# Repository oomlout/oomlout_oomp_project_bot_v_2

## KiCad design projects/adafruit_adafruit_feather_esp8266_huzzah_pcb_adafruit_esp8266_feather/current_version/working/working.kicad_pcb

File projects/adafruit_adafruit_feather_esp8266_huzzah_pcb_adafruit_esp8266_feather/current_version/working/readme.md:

# adafruit_feather_esp8266_huzzah_pcb
 
## summary 
* id: adafruit_adafruit_feather_esp8266_huzzah_pcb_adafruit_esp8266_feather
* user: adafruit
* name: adafruit_feather_esp8266_huzzah_pcb
* board: adafruit_esp8266_feather
* repo: https://github.com/adafruit/Adafruit-Feather-ESP8266-HUZZAH-PCB

* src_file_repo_sch: 
* src_file_repo_sch_link: https://github.com/adafruit/Adafruit-Feather-ESP8266-HUZZAH-PCB/tree/master/
* full details link: https://github.com/oomlout/oomlout_oomp_project_bot_v_2/tree/main/projects/adafruit_adafruit_feather_esp8266_huzzah_pcb_adafruit_esp8266_feather/current_version/working  

## schematic  
  
[schematic (pdf)](working_schematic.pdf) 

## pcb  

[board (pdf)](working.pdf)  

## working_bom
| Id | Designator | Footprint | Quantity | Designation | Supplier and ref |  | None | 
| --- | --- | --- | --- | --- | --- | --- | --- | 
| 1 | R2,R10 | 0603-NO | 2 | 1K |  |  | [''] | 
| 2 | CHG0 | CHIPLED_0805_NOOUTLINE | 1 | ORANGE |  |  | [''] | 
| 3 | JP1 | 1X16_ROUND | 1 |  |  |  | [''] | 
| 4 | R3,R5,R9,R4,R1,R7 | 0603-NO | 6 | 10K |  |  | [''] | 
| 5 | X4 | 4UCONN_20329_V2 | 1 | 20329 |  |  | [''] | 
| 6 | U$34,U$35 | FIDUCIAL_1MM | 2 | FIDUCIAL_1MM |  |  | [''] | 
| 7 | IC1 | QFN24_4MM_SMSC | 1 | CP2104 |  |  | [''] | 
| 8 | U$31,U$32 | MOUNTINGHOLE_2.5_PLATED | 2 | MOUNTINGHOLE2.5 |  |  | [''] | 
| 9 | @HOLE0,@HOLE1 |  | 2 |  |  |  | [''] | 
| 10 | X2 | ESP-12S | 1 | ESP-12 |  |  | [''] | 
| 11 | Q2,Q1 | SOT23-3 | 2 | mmbt2222 |  |  | [''] | 
| 12 | C3,C6,C8 | 0805-NO | 3 | 10ÂµF |  |  | [''] | 
| 13 | R11 | _0603MP | 1 | 1K |  |  | [''] | 
| 14 | D3 | CHIPLED_0805_NOOUTLINE | 1 | RED |  |  | [''] | 
| 15 | R6 | 0603-NO | 1 | 4.7K |  |  | [''] | 
| 16 | U2 | SOT23-5 | 1 | AP2112-3.3 |  |  | [''] | 
| 17 | X1 | JSTPH2 | 1 | JSTPH |  |  | [''] | 
| 18 | SW2 | BTN_KMR2_4.6X2.8 | 1 | KMR2 |  |  | [''] | 
| 19 | D4 | SOD-123 | 1 | MBR120 |  |  | [''] | 
| 20 | SJ1 | SOLDERJUMPER_CLOSEDWIRE | 1 |  |  |  | [''] | 
| 21 | JP3 | 1X12_ROUND | 1 |  |  |  | [''] | 
| 22 | U$15 | ADAFRUIT_3.5MM | 1 |  |  |  | [''] | 
| 23 | R8 | 0603-NO | 1 | 10K\ |  |  | [''] | 
| 24 | C7 | 0603-NO | 1 | 1uF |  |  | [''] | 
| 25 | U3 | SOT23-5 | 1 | MCP73831T-2ACI/OT |  |  | [''] | 
| 26 | C2 | 0805-NO | 1 | 10uF |  |  | [''] | 
| 27 | U$23 | HUZZAHLOGO | 1 |  |  |  | [''] | 
| 28 | U$13 | PCBFEAT-REV-040 | 1 |  |  |  | [''] | 
| 29 | U$7 | ADAFRUIT_5MM | 1 |  |  |  | [''] | 
| 30 | U$9 | FEATHERLOGO | 1 |  |  |  | [''] | 

## bom_schematic
| Ref | Qnty | Value | Cmp name | Footprint | Description | Vendor | DNP | 
| --- | --- | --- | --- | --- | --- | --- | --- | 
| C2 | 1 | 10uF | CAP_CERAMIC0805-NOOUTLINE | working:0805-NO |  |  |  | 
| C3, C6, C8 | 3 | 10ÂµF | CAP_CERAMIC0805-NOOUTLINE | working:0805-NO |  |  |  | 
| C7 | 1 | 1uF | CAP_CERAMIC0603_NO | working:0603-NO |  |  |  | 
| CHG0 | 1 | ORANGE | LED0805_NOOUTLINE | working:CHIPLED_0805_NOOUTLINE |  |  |  | 
| D3 | 1 | RED | LED0805_NOOUTLINE | working:CHIPLED_0805_NOOUTLINE |  |  |  | 
| D4 | 1 | MBR120 | DIODE-SCHOTTKYSOD-123 | working:SOD-123 |  |  |  | 
| IC1 | 1 | CP2104 | CP2104 | working:QFN24_4MM_SMSC |  |  |  | 
| JP1 | 1 | HEADER-1X16ROUND | HEADER-1X16ROUND | working:1X16_ROUND |  |  |  | 
| JP3 | 1 | HEADER-1X12 | HEADER-1X12 | working:1X12_ROUND |  |  |  | 
| Q1, Q2 | 2 | mmbt2222 | TRANSISTOR_NPNSOT23-3 | working:SOT23-3 |  |  |  | 
| R1, R3, R4, R5, R7, R9 | 6 | 10K | RESISTOR_0603_NOOUT | working:0603-NO |  |  |  | 
| R2, R10 | 2 | 1K | RESISTOR_0603_NOOUT | working:0603-NO |  |  |  | 
| R6 | 1 | 4.7K | RESISTOR_0603_NOOUT | working:0603-NO |  |  |  | 
| R8 | 1 | 10K\ | RESISTOR_0603_NOOUT | working:0603-NO |  |  |  | 
| R11 | 1 | 1K | RESISTOR_0603MP | working:_0603MP |  |  |  | 
| SJ1 | 1 | SOLDERJUMPER_CLOSED | SOLDERJUMPER_CLOSED | working:SOLDERJUMPER_CLOSEDWIRE |  |  |  | 
| SW2 | 1 | KMR2 | SWITCH_TACT_SMT4.6X2.8 | working:BTN_KMR2_4.6X2.8 |  |  |  | 
| U2 | 1 | AP2112-3.3 | VREG_SOT23-5 | working:SOT23-5 |  |  |  | 
| U3 | 1 | MCP73831T-2ACI/OT | MCP73831/2 | working:SOT23-5 |  |  |  | 
| U$31, U$32 | 2 | MOUNTINGHOLE2.5 | MOUNTINGHOLE2.5 | working:MOUNTINGHOLE_2.5_PLATED |  |  |  | 
| U$34, U$35 | 2 | FIDUCIAL_1MM | FIDUCIAL_1MM | working:FIDUCIAL_1MM |  |  |  | 
| X1 | 1 | JSTPH | CON_JST_PH_2PIN | working:JSTPH2 |  |  |  | 
| X2 | 1 | ESP-12S | ESP-12S | working:ESP-12S |  |  |  | 
| X4 | 1 | 20329 | USB_MICRO_20329_V2 | working:4UCONN_20329_V2 |  |  |  | 

## mounting_holes
| x | y | package | value | ref | size | 
| --- | --- | --- | --- | --- | --- | 
| 0.0 | 17.78 | MOUNTINGHOLE_2.5_PLATED | MOUNTINGHOLE2.5 | U$31 | m3 | 
| 0.0 | 0.0 | MOUNTINGHOLE_2.5_PLATED | MOUNTINGHOLE2.5 | U$32 | m3 |

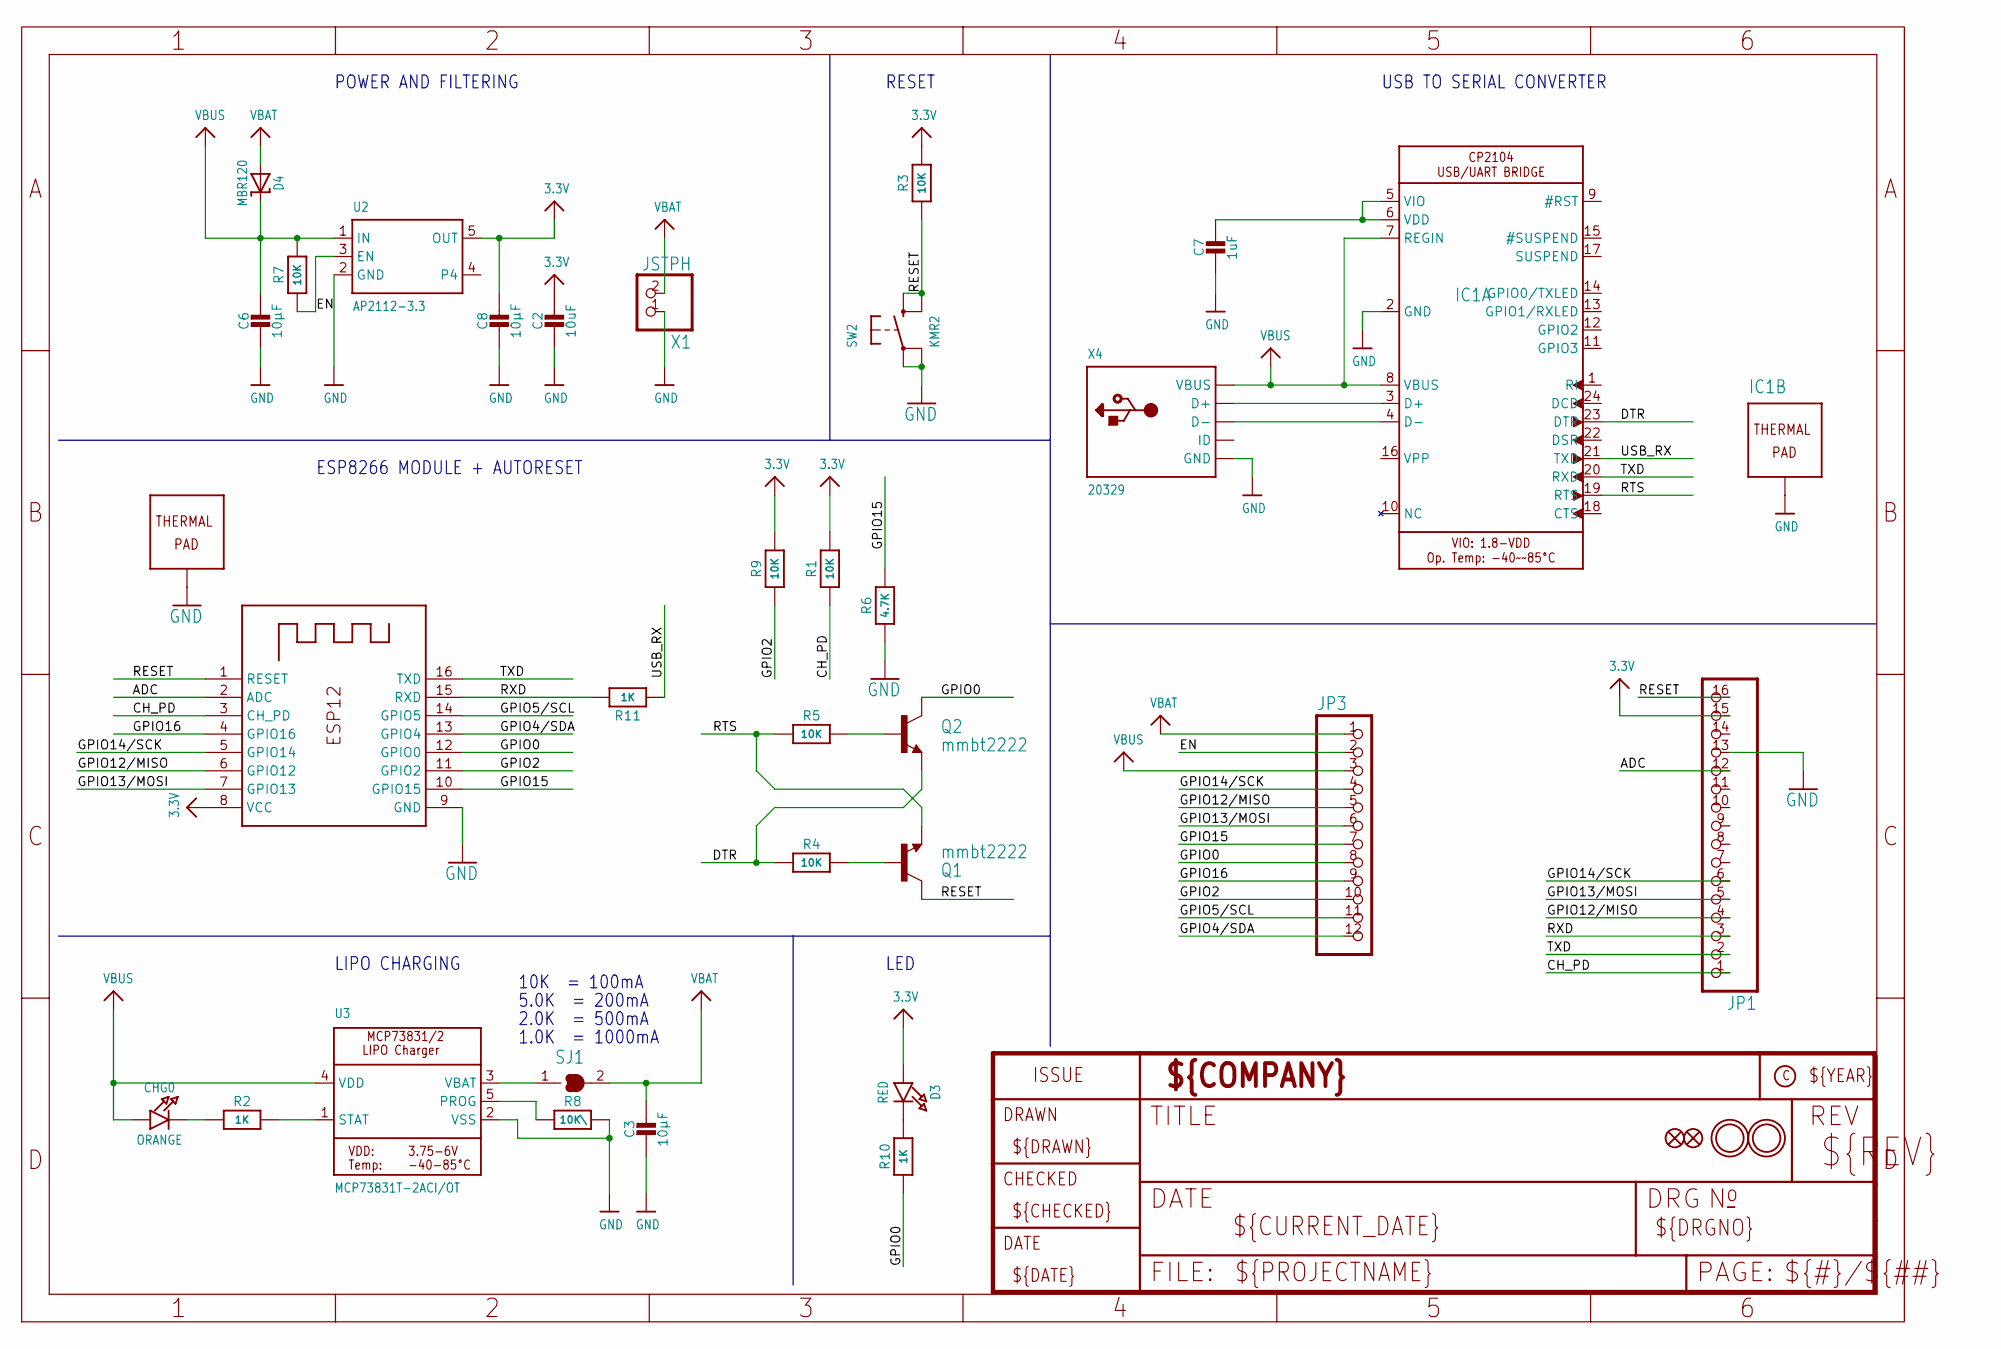
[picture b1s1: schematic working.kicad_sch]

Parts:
C2: 10uF; 0805-NO
C3, C6, C8: 10µF; 0805-NO
C7: 1uF; 0603-NO
CHG0: ORANGE; CHIPLED_0805_NOOUTLINE
D3: RED; CHIPLED_0805_NOOUTLINE
D4: MBR120; SOD-123
IC1: CP2104; QFN24_4MM_SMSC
JP1: HEADER-1X16ROUND; 1X16_ROUND
JP3: HEADER-1X12; 1X12_ROUND
Q1, Q2: mmbt2222; SOT23-3
R1, R3, R4, R5, R7, R9: 10K; 0603-NO
R2, R10: 1K; 0603-NO
R6: 4.7K; 0603-NO
R8: 10K\; 0603-NO
R11: 1K; _0603MP
SJ1: SOLDERJUMPER_CLOSED; SOLDERJUMPER_CLOSEDWIRE
SW2: KMR2; BTN_KMR2_4.6X2.8
U2: AP2112-3.3; SOT23-5
U3: MCP73831T-2ACI/OT; SOT23-5
U$31, U$32: MOUNTINGHOLE2.5; MOUNTINGHOLE_2.5_PLATED
U$34, U$35: FIDUCIAL_1MM
X1: JSTPH; JSTPH2
X2: ESP-12S
X4: 20329; 4UCONN_20329_V2

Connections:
3.3V: C2.1, C8.1, D3.A, JP1.15, R1.2, R3.2, R9.2, U2.5 (OUT), X2.8 (VCC)
ADC: JP1.12, X2.2 (ADC)
CH_PD: JP1.1, R1.1, X2.3 (CH_PD)
DTR: IC1.23 (DTR), Q2.2 (E), R4.1
EN: JP3.2, R7.1, U2.3 (EN)
GND: C2.2, C3.2, C6.2, C7.2, C8.2, IC1.2 (GND), IC1.THERM (TP), JP1.13, R6.1, R8.2, SW2.A, SW2.A' (P1), U2.2 (GND), U3.2 (VSS), X1.1, X2.9 (GND), X2.P$1 (TP), X4.BASE@1 (GND), X4.BASE@2 (GND), X4.GND, X4.SPRT@1 (GND), X4.SPRT@2 (GND), X4.SPRT@3 (GND), X4.SPRT@4 (GND)
GPIO0: JP3.8, Q2.3 (C), R10.1, X2.12 (GPIO0)
GPIO2: JP3.10, R9.1, X2.11 (GPIO2)
GPIO4/SDA: JP3.12, X2.13 (GPIO4)
GPIO5/SCL: JP3.11, X2.14 (GPIO5)
GPIO12/MISO: JP1.4, JP3.5, X2.6 (GPIO12)
GPIO13/MOSI: JP1.5, JP3.6, X2.7 (GPIO13)
GPIO14/SCK: JP1.6, JP3.4, X2.5 (GPIO14)
GPIO15: JP3.7, R6.2, X2.10 (GPIO15)
GPIO16: JP3.9, X2.4 (GPIO16)
unnamed: CHG0.C, R2.1
unnamed: IC1.3 (D+), X4.D+
unnamed: R2.2, U3.1 (STAT)
unnamed: R8.1, U3.5 (PROG)
unnamed: D3.C, R10.2
unnamed: IC1.4 (D-), X4.D-
unnamed: SJ1.1, U3.3 (VBAT)
unnamed: C7.1, IC1.5 (VIO), IC1.6 (VDD)
unnamed: Q1.1 (B), R4.2
unnamed: Q2.1 (B), R5.2
RESET: JP1.16, Q1.3 (C), R3.1, SW2.B (S), SW2.B' (S1), X2.1 (RESET)
RTS: IC1.19 (RTS), Q1.2 (E), R5.1
RXD: JP1.3, R11.2, X2.15 (RXD)
TXD: IC1.20 (RXD), JP1.2, X2.16 (TXD)
USB_RX: IC1.21 (TXD), R11.1
VBAT: C3.1, D4.A, JP3.1, SJ1.2, X1.2
VBUS: C6.1, CHG0.A, D4.C, IC1.7 (REGIN), IC1.8 (VBUS), JP3.3, R7.2, U2.1 (IN), U3.4 (VDD), X4.VBUS

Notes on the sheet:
10K = 100mA
POWER AND FILTERING
1.0K = 1000mA
5.0K = 200mA
USB TO SERIAL CONVERTER
2.0K = 500mA
LED
ESP8266 MODULE + AUTORESET
RESET
LIPO CHARGING

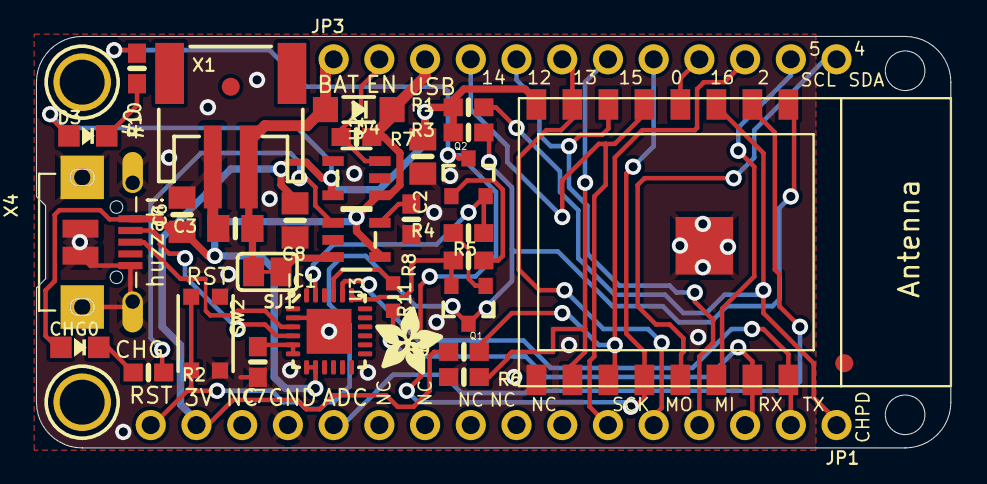
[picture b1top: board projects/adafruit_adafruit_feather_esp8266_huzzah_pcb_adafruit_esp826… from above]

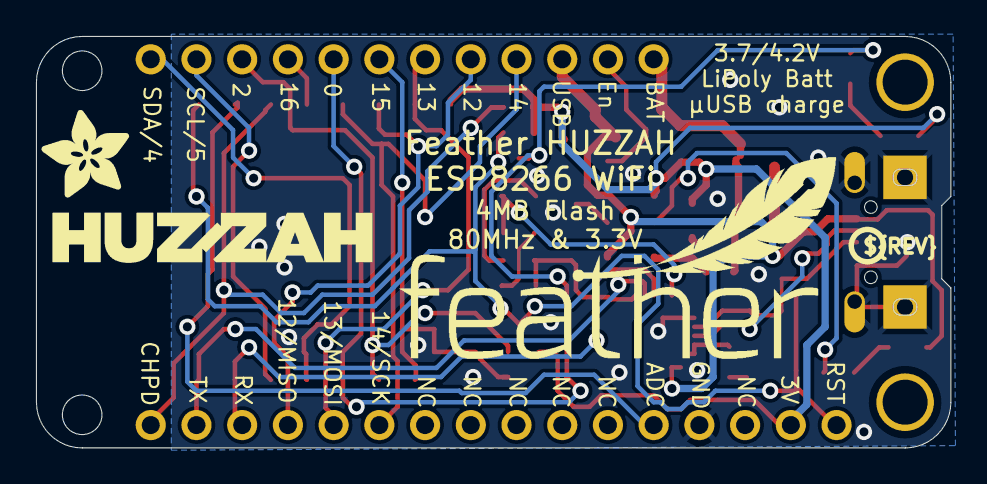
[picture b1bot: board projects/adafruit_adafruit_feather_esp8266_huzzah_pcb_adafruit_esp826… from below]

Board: 2 copper layers, 50.8 x 22.9 mm, 42 parts (4 on the bottom side), 32 nets.

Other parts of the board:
@HOLE0, @HOLE1: (no value)
U$7: ADAFRUIT_5MM
U$9: FEATHERLOGO
U$13: PCBFEAT-REV-040
U$15: ADAFRUIT_3.5MM
U$23: HUZZAHLOGO

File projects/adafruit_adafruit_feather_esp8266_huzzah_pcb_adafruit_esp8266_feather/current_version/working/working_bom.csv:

"Id";"Designator";"Footprint";"Quantity";"Designation";"Supplier and ref";
1;"R2,R10";"0603-NO";2;"1K";;;
2;"CHG0";"CHIPLED_0805_NOOUTLINE";1;"ORANGE";;;
3;"JP1";"1X16_ROUND";1;"";;;
4;"R3,R5,R9,R4,R1,R7";"0603-NO";6;"10K";;;
5;"X4";"4UCONN_20329_V2";1;"20329";;;
6;"U$34,U$35";"FIDUCIAL_1MM";2;"FIDUCIAL_1MM";;;
7;"IC1";"QFN24_4MM_SMSC";1;"CP2104";;;
8;"U$31,U$32";"MOUNTINGHOLE_2.5_PLATED";2;"MOUNTINGHOLE2.5";;;
9;"@HOLE0,@HOLE1";"";2;"";;;
10;"X2";"ESP-12S";1;"ESP-12";;;
11;"Q2,Q1";"SOT23-3";2;"mmbt2222";;;
12;"C3,C6,C8";"0805-NO";3;"10µF";;;
13;"R11";"_0603MP";1;"1K";;;
14;"D3";"CHIPLED_0805_NOOUTLINE";1;"RED";;;
15;"R6";"0603-NO";1;"4.7K";;;
16;"U2";"SOT23-5";1;"AP2112-3.3";;;
17;"X1";"JSTPH2";1;"JSTPH";;;
18;"SW2";"BTN_KMR2_4.6X2.8";1;"KMR2";;;
19;"D4";"SOD-123";1;"MBR120";;;
20;"SJ1";"SOLDERJUMPER_CLOSEDWIRE";1;"";;;
21;"JP3";"1X12_ROUND";1;"";;;
22;"U$15";"ADAFRUIT_3.5MM";1;"";;;
23;"R8";"0603-NO";1;"10K\";;;
24;"C7";"0603-NO";1;"1uF";;;
25;"U3";"SOT23-5";1;"MCP73831T-2ACI/OT";;;
26;"C2";"0805-NO";1;"10uF";;;
27;"U$23";"HUZZAHLOGO";1;"";;;
28;"U$13";"PCBFEAT-REV-040";1;"";;;
29;"U$7";"ADAFRUIT_5MM";1;"";;;
30;"U$9";"FEATHERLOGO";1;"";;;

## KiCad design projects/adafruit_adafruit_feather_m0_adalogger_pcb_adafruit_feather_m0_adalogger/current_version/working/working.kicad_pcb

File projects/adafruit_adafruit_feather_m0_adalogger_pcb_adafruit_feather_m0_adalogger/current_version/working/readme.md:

# adafruit_feather_m0_adalogger_pcb
 
## summary 
* id: adafruit_adafruit_feather_m0_adalogger_pcb_adafruit_feather_m0_adalogger
* user: adafruit
* name: adafruit_feather_m0_adalogger_pcb
* board: adafruit_feather_m0_adalogger
* repo: https://github.com/adafruit/Adafruit-Feather-M0-Adalogger-PCB

* src_file_repo_sch: 
* src_file_repo_sch_link: https://github.com/adafruit/Adafruit-Feather-M0-Adalogger-PCB/tree/master/
* full details link: https://github.com/oomlout/oomlout_oomp_project_bot_v_2/tree/main/projects/adafruit_adafruit_feather_m0_adalogger_pcb_adafruit_feather_m0_adalogger/current_version/working  

## schematic  
  
[schematic (pdf)](working_schematic.pdf) 

## pcb  

[board (pdf)](working.pdf)  

## working_bom
| Id | Designator | Footprint | Quantity | Designation | Supplier and ref |  | None | 
| --- | --- | --- | --- | --- | --- | --- | --- | 
| 1 | C5 | 0805-NO | 1 | 10uF |  |  | [''] | 
| 2 | CHG0 | CHIPLED_0805_NOOUTLINE | 1 | ORANGE |  |  | [''] | 
| 3 | C6,C8,C3 | 0805-NO | 3 | 10ÂµF |  |  | [''] | 
| 4 | X4 | MICROSD | 1 | microsd |  |  | [''] | 
| 5 | SW1 | KMR2 | 1 | SPST_TACT-KMR2 |  |  | [''] | 
| 6 | R6 | 0603-NO | 1 | 100K |  |  | [''] | 
| 7 | C7,C1,C14 | 0603-NO | 3 | 1uF |  |  | [''] | 
| 8 | C4,C2 | 0603-NO | 2 | 22pF |  |  | [''] | 
| 9 | R3,R1 | 0603-NO | 2 | 100k |  |  | [''] | 
| 10 | X2 | XTAL3215 | 1 | 32.768 |  |  | [''] | 
| 11 | @HOLE1,@HOLE0 |  | 2 |  |  |  | [''] | 
| 12 | U$34,U$35 | FIDUCIAL_1MM | 2 | FIDUCIAL" |  |  | [''] | 
| 13 | U$7 | ADAFRUIT_3.5MM | 1 |  |  |  | [''] | 
| 14 | U2 | SOT23-5 | 1 | SPX3819-3.3 |  |  | [''] | 
| 15 | U$31,U$32 | MOUNTINGHOLE_2.5_PLATED | 2 | MOUNTINGHOLE2.5 |  |  | [''] | 
| 16 | JP1 | 1X16_ROUND | 1 |  |  |  | [''] | 
| 17 | L0 | CHIPLED_0805_NOOUTLINE | 1 | RED |  |  | [''] | 
| 18 | L1 | CHIPLED_0805_NOOUTLINE | 1 | GREEN |  |  | [''] | 
| 19 | X3 | 4UCONN_20329_V2 | 1 | microUSB |  |  | [''] | 
| 20 | R4,R2 | 0603-NO | 2 | 1K |  |  | [''] | 
| 21 | JP3 | 1X12_ROUND | 1 |  |  |  | [''] | 
| 22 | U$9 | PCBFEAT-REV-040 | 1 |  |  |  | [''] | 
| 23 | D1 | SOD-123 | 1 | MBR120 |  |  | [''] | 
| 24 | R7 | 0603-NO | 1 | 2.2K |  |  | [''] | 
| 25 | U3 | SOT23-5 | 1 | MCP73831T-2ACI/OT |  |  | [''] | 
| 26 | X1 | JSTPH2 | 1 | JSTPH |  |  | [''] | 
| 27 | R8 | 0603-NO | 1 | 10K\ |  |  | [''] | 
| 28 | U$4 | TQFN48_7MM | 1 | ATSAMD21G18_QFN |  |  | [''] | 
| 29 | U$14 | ADALOGGER_LOGO | 1 |  |  |  | [''] | 
| 30 | TP1,TP2 | TESTPOINT_ROUND_1.5MM | 2 |  |  |  | [''] | 
| 31 | U$13 | FEATHERLOGO | 1 |  |  |  | [''] | 

## bom_schematic
| Ref | Qnty | Value | Cmp name | Footprint | Description | Vendor | DNP | 
| --- | --- | --- | --- | --- | --- | --- | --- | 
| C1, C7, C14 | 3 | 1uF | CAP_CERAMIC0603_NO | working:0603-NO |  |  |  | 
| C2, C4 | 2 | 22pF | CAP_CERAMIC0603_NO | working:0603-NO |  |  |  | 
| C3, C6, C8 | 3 | 10ÂµF | CAP_CERAMIC0805-NOOUTLINE | working:0805-NO |  |  |  | 
| C5 | 1 | 10uF | CAP_CERAMIC0805-NOOUTLINE | working:0805-NO |  |  |  | 
| CHG0 | 1 | ORANGE | LED0805_NOOUTLINE | working:CHIPLED_0805_NOOUTLINE |  |  |  | 
| D1 | 1 | MBR120 | DIODE-SCHOTTKYSOD-123 | working:SOD-123 |  |  |  | 
| JP1 | 1 | HEADER-1X16ROUND | HEADER-1X16ROUND | working:1X16_ROUND |  |  |  | 
| JP3 | 1 | HEADER-1X12 | HEADER-1X12 | working:1X12_ROUND |  |  |  | 
| L0 | 1 | RED | LED0805_NOOUTLINE | working:CHIPLED_0805_NOOUTLINE |  |  |  | 
| L1 | 1 | GREEN | LED0805_NOOUTLINE | working:CHIPLED_0805_NOOUTLINE |  |  |  | 
| R1, R3 | 2 | 100k | RESISTOR_0603_NOOUT | working:0603-NO |  |  |  | 
| R2, R4 | 2 | 1K | RESISTOR_0603_NOOUT | working:0603-NO |  |  |  | 
| R6 | 1 | 100K | RESISTOR_0603_NOOUT | working:0603-NO |  |  |  | 
| R7 | 1 | 2.2K | RESISTOR_0603_NOOUT | working:0603-NO |  |  |  | 
| R8 | 1 | 10K\ | RESISTOR_0603_NOOUT | working:0603-NO |  |  |  | 
| SW1 | 1 | SPST_TACT-KMR2 | SPST_TACT-KMR2 | working:KMR2 |  |  |  | 
| TP1, TP2 | 2 | TESTPOINTROUND1.5MM | TESTPOINTROUND1.5MM | working:TESTPOINT_ROUND_1.5MM |  |  |  | 
| U2 | 1 | SPX3819-3.3 | VREG_SOT23-5 | working:SOT23-5 |  |  |  | 
| U3 | 1 | MCP73831T-2ACI/OT | MCP73831/2 | working:SOT23-5 |  |  |  | 
| U$4 | 1 | ATSAMD21J_QFN | ATSAMD21J_QFN | working:TQFN48_7MM |  |  |  | 
| U$31, U$32 | 2 | MOUNTINGHOLE2.5 | MOUNTINGHOLE2.5 | working:MOUNTINGHOLE_2.5_PLATED |  |  |  | 
| U$34, U$35 | 2 | FIDUCIAL"" | FIDUCIAL{dblquote}{dblquote} | working:FIDUCIAL_1MM |  |  |  | 
| X1 | 1 | JSTPH | CON_JST_PH_2PIN | working:JSTPH2 |  |  |  | 
| X2 | 1 | 32.768 | XTAL-3.2X1.5 | working:XTAL3215 |  |  |  | 
| X3 | 1 | microUSB | USB_MICRO_20329_V2 | working:4UCONN_20329_V2 |  |  |  | 
| X4 | 1 | microsd | MICROSD | working:MICROSD |  |  |  | 

## mounting_holes
| x | y | package | value | ref | size | 
| --- | --- | --- | --- | --- | --- | 
| 0.0 | 17.78 | MOUNTINGHOLE_2.5_PLATED | MOUNTINGHOLE2.5 | U$31 | m3 | 
| 0.0 | 0.0 | MOUNTINGHOLE_2.5_PLATED | MOUNTINGHOLE2.5 | U$32 | m3 |

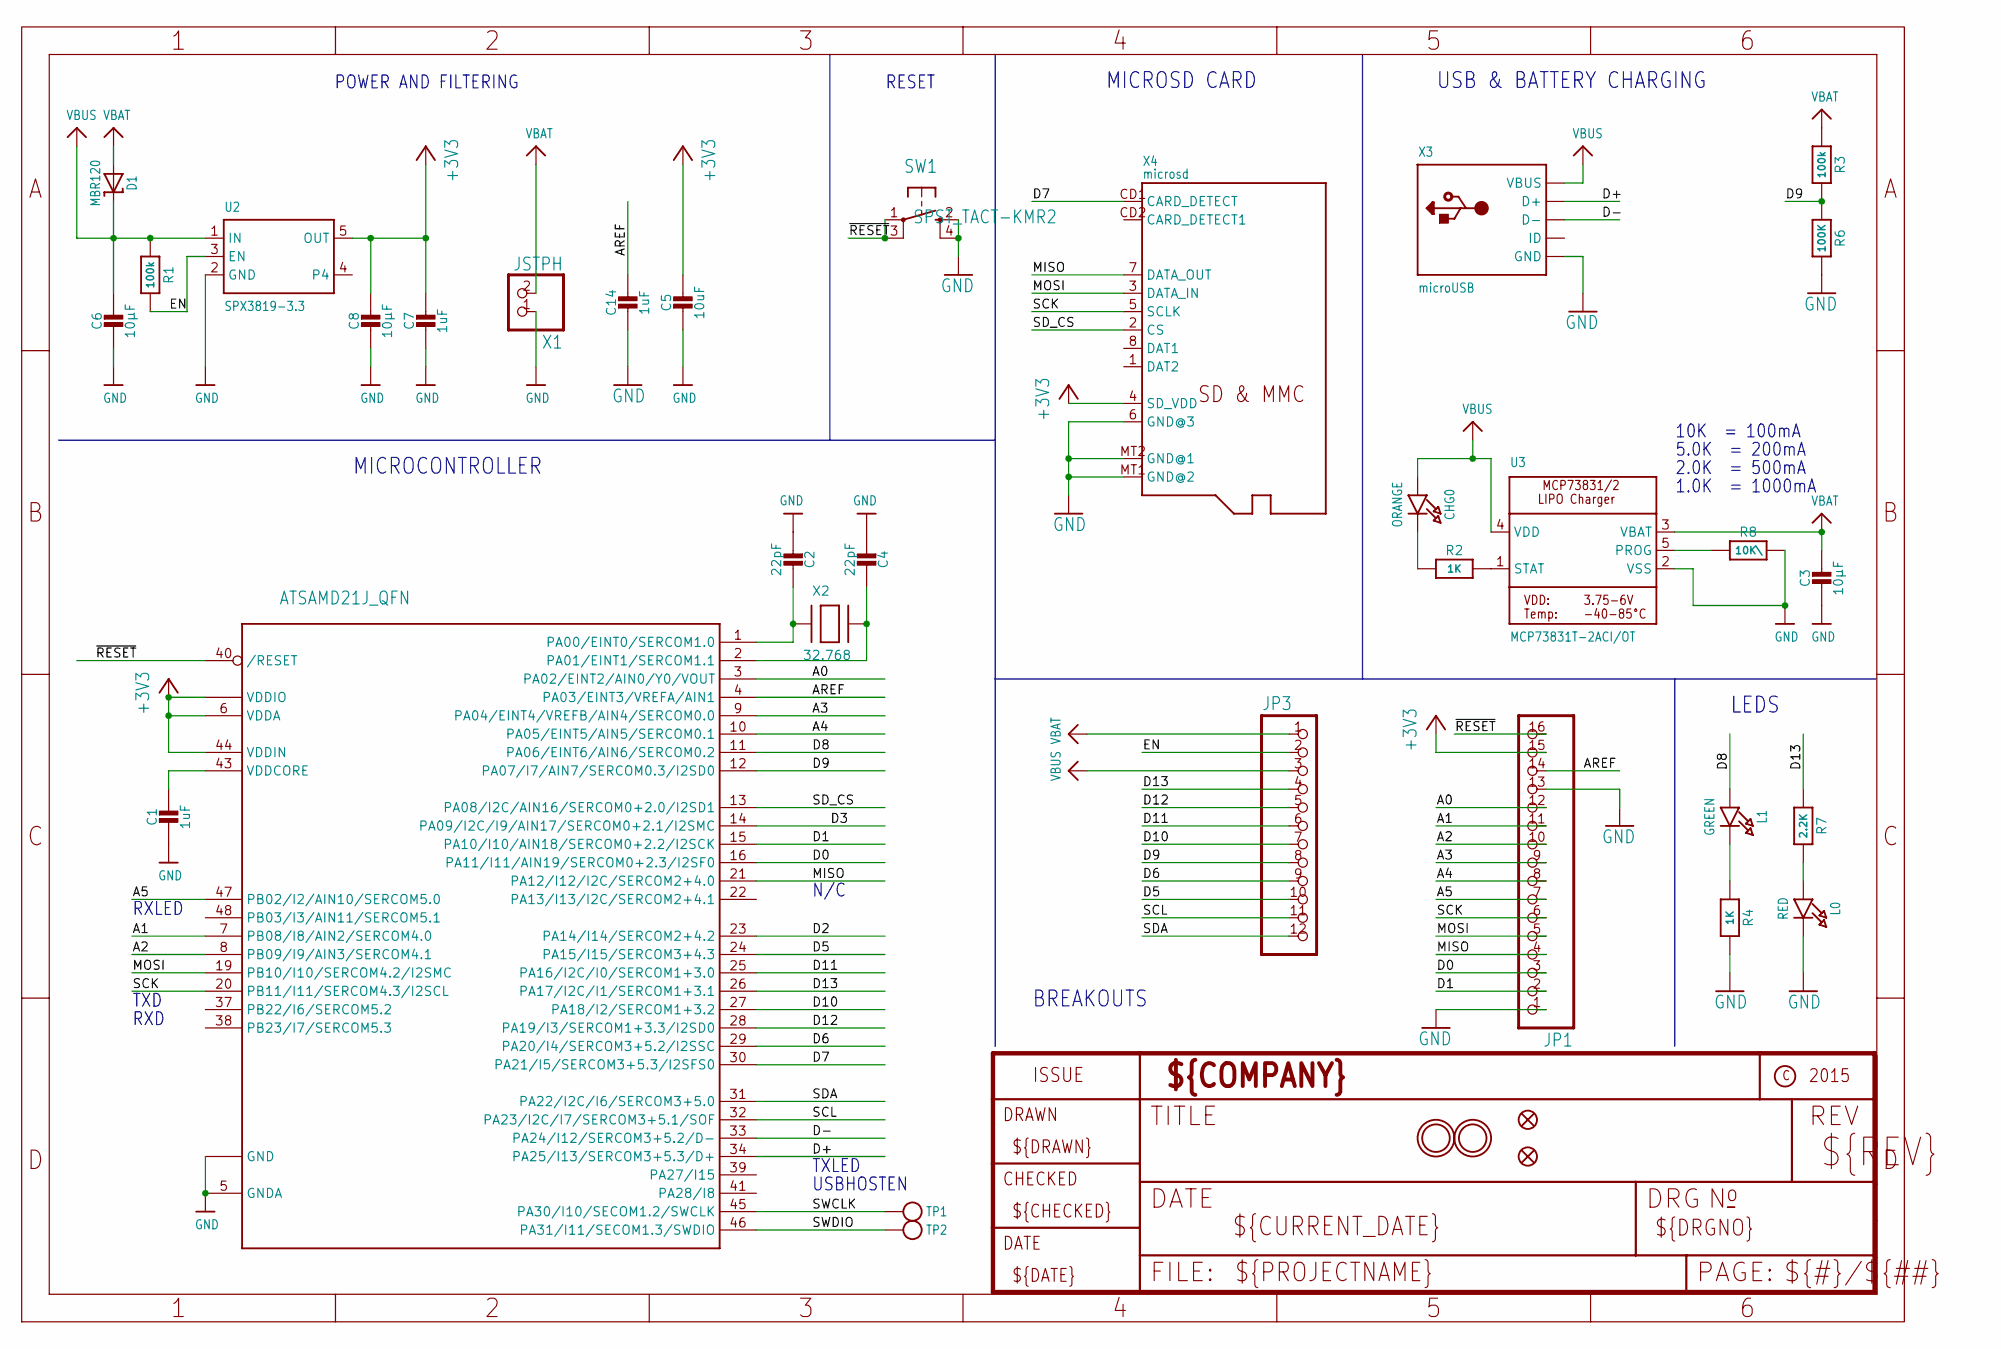
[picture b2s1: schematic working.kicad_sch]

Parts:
C1, C7, C14: 1uF; 0603-NO
C2, C4: 22pF; 0603-NO
C3, C6, C8: 10µF; 0805-NO
C5: 10uF; 0805-NO
CHG0: ORANGE; CHIPLED_0805_NOOUTLINE
D1: MBR120; SOD-123
JP1: HEADER-1X16ROUND; 1X16_ROUND
JP3: HEADER-1X12; 1X12_ROUND
L0: RED; CHIPLED_0805_NOOUTLINE
L1: GREEN; CHIPLED_0805_NOOUTLINE
R1, R3: 100k; 0603-NO
R2, R4: 1K; 0603-NO
R6: 100K; 0603-NO
R7: 2.2K; 0603-NO
R8: 10K\; 0603-NO
SW1: SPST_TACT-KMR2; KMR2
TP1, TP2: TESTPOINTROUND1.5MM; TESTPOINT_ROUND_1.5MM
U2: SPX3819-3.3; SOT23-5
U3: MCP73831T-2ACI/OT; SOT23-5
U$4: ATSAMD21J_QFN; TQFN48_7MM
U$31, U$32: MOUNTINGHOLE2.5; MOUNTINGHOLE_2.5_PLATED
U$34, U$35: FIDUCIAL""; FIDUCIAL_1MM
X1: JSTPH; JSTPH2
X2: 32.768; XTAL3215
X3: microUSB; 4UCONN_20329_V2
X4: microsd; MICROSD

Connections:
+3V3: C5.1, C7.1, C8.1, JP1.15, U2.5 (OUT), U$4.6 (VDDA), U$4.17 (VDDIO), U$4.36 (VDDIO), U$4.44 (VDDIN), X4.4 (SD_VDD)
A0: JP1.12, U$4.3 (PA02/EINT2/AIN0/Y0/VOUT)
A1: JP1.11, U$4.7 (PB08/I8/AIN2/SERCOM4.0)
A2: JP1.10, U$4.8 (PB09/I9/AIN3/SERCOM4.1)
A3: JP1.9, U$4.9 (PA04/EINT4/VREFB/AIN4/SERCOM0.0)
A4: JP1.8, U$4.10 (PA05/EINT5/AIN5/SERCOM0.1)
A5: JP1.7, U$4.47 (PB02/I2/AIN10/SERCOM5.0)
AREF: C14.1, JP1.14, U$4.4 (PA03/EINT3/VREFA/AIN1)
D0: JP1.3, U$4.16 (PA11/I11/AIN19/SERCOM0+2.3/I2SF0)
D1: JP1.2, U$4.15 (PA10/I10/AIN18/SERCOM0+2.2/I2SCK)
D2: U$4.23 (PA14/I14/SERCOM2+4.2)
D3: U$4.14 (PA09/I2C/I9/AIN17/SERCOM0+2.1/I2SMC)
D5: JP3.10, U$4.24 (PA15/I15/SERCOM3+4.3)
D6: JP3.9, U$4.29 (PA20/I4/SERCOM3+5.2/I2SSC)
D7: U$4.30 (PA21/I5/SERCOM3+5.3/I2SFS0), X4.CD1 (CARD_DETECT)
D8: L1.A, U$4.11 (PA06/EINT6/AIN6/SERCOM0.2)
D9: JP3.8, R3.2, R6.1, U$4.12 (PA07/I7/AIN7/SERCOM0.3/I2SD0)
D10: JP3.7, U$4.27 (PA18/I2/SERCOM1+3.2)
D11: JP3.6, U$4.25 (PA16/I2C/I0/SERCOM1+3.0)
D12: JP3.5, U$4.28 (PA19/I3/SERCOM1+3.3/I2SD0)
D13: JP3.4, R7.1, U$4.26 (PA17/I2C/I1/SERCOM1+3.1)
D+: U$4.34 (PA25/I13/SERCOM3+5.3/D+), X3.D+
D-: U$4.33 (PA24/I12/SERCOM3+5.2/D-), X3.D-
EN: JP3.2, R1.2, U2.3 (EN)
GND: C1.2, C2.2, C3.2, C4.2, C5.2, C6.2, C7.2, C8.2, C14.2, JP1.1, JP1.13, L0.C, R4.2, R6.2, R8.2, SW1.2 (S), SW1.4 (S1), U2.2 (GND), U3.2 (VSS), U$4.5 (GNDA), U$4.18 (GND), U$4.35 (GND), U$4.42 (GND), U$4.THERMAL (GND), X1.1, X3.BASE@1 (GND), X3.BASE@2 (GND), X3.GND, X3.SPRT@1 (GND), X3.SPRT@2 (GND), X3.SPRT@3 (GND), X3.SPRT@4 (GND), X4.6 (GND@3), X4.MT1 (GND@2), X4.MT2 (GND@1)
MISO: JP1.4, U$4.21 (PA12/I12/I2C/SERCOM2+4.0), X4.7 (DATA_OUT)
MOSI: JP1.5, U$4.19 (PB10/I10/SERCOM4.2/I2SMC), X4.3 (DATA_IN)
unnamed: CHG0.C, R2.1
unnamed: L0.A, R7.2
unnamed: R2.2, U3.1 (STAT)
unnamed: R8.1, U3.5 (PROG)
unnamed: C2.1, U$4.1 (PA00/EINT0/SERCOM1.0), X2.P$1
unnamed: L1.C, R4.1
unnamed: C4.1, U$4.2 (PA01/EINT1/SERCOM1.1), X2.P$2
SCK: JP1.6, U$4.20 (PB11/I11/SERCOM4.3/I2SCL), X4.5 (SCLK)
SCL: JP3.11, U$4.32 (PA23/I2C/I7/SERCOM3+5.1/SOF)
SDA: JP3.12, U$4.31 (PA22/I2C/I6/SERCOM3+5.0)
SD_CS: U$4.13 (PA08/I2C/AIN16/SERCOM0+2.0/I2SD1), X4.2 (CS)
SWCLK: TP1.P$1, U$4.45 (PA30/I10/SECOM1.2/SWCLK)
SWDIO: TP2.P$1, U$4.46 (PA31/I11/SECOM1.3/SWDIO)
VBAT: C3.1, D1.A, JP3.1, R3.1, U3.3 (VBAT), X1.2
VBUS: C6.1, CHG0.A, D1.C, JP3.3, R1.1, U2.1 (IN), U3.4 (VDD), X3.VBUS
VDDCORE: C1.1, U$4.43 (VDDCORE)
~RESET: JP1.16, SW1.1, SW1.3 (P1), U$4.40 (/RESET)

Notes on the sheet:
10K = 100mA
MICROSD CARD
USBHOSTEN
RXLED
TXLED
5.0K = 200mA
POWER AND FILTERING
USB & BATTERY CHARGING
N/C
2.0K = 500mA
RXD
1.0K = 1000mA
BREAKOUTS
LEDS
MICROCONTROLLER
RESET
TXD

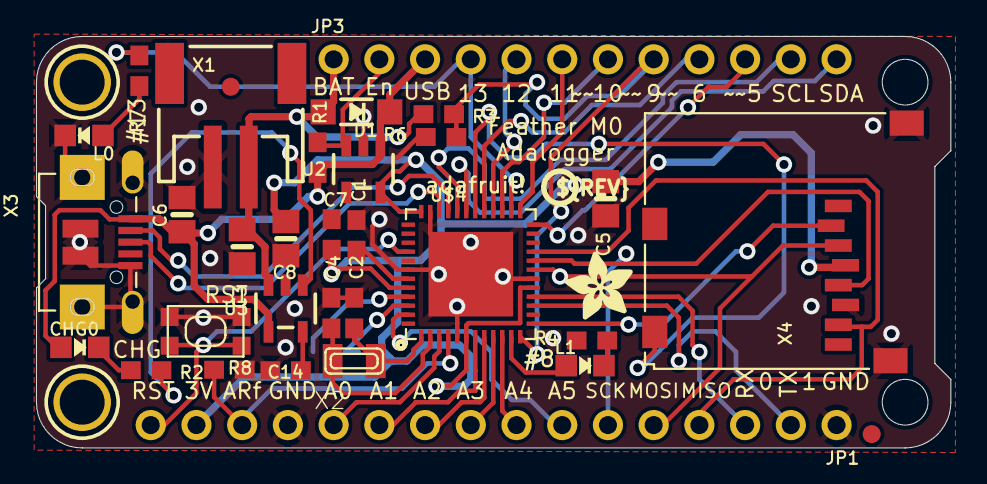
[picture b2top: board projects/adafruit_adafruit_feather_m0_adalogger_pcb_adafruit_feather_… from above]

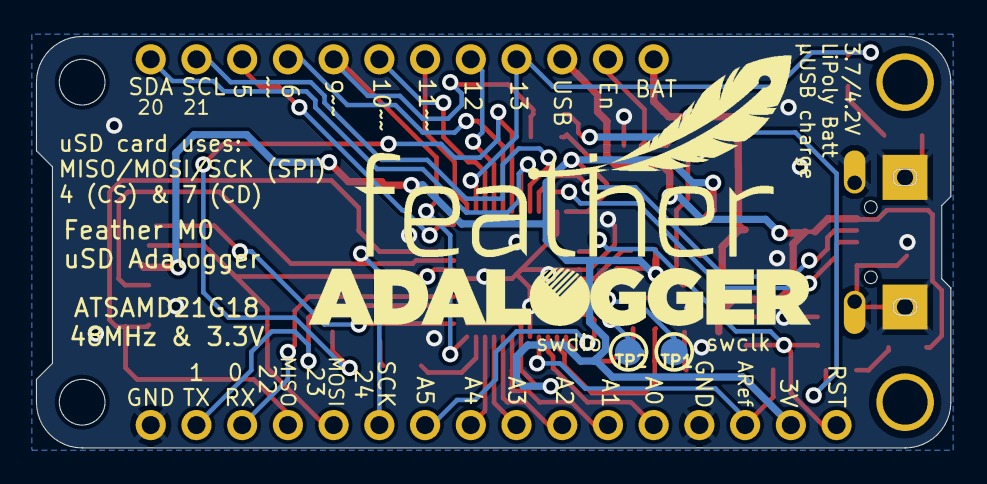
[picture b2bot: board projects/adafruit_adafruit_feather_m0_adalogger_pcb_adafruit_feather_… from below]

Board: 2 copper layers, 50.8 x 22.9 mm, 42 parts (4 on the bottom side), 42 nets.

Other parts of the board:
@HOLE0, @HOLE1: (no value)
U$7: ADAFRUIT_3.5MM
U$9: PCBFEAT-REV-040
U$13: FEATHERLOGO
U$14: ADALOGGER_LOGO

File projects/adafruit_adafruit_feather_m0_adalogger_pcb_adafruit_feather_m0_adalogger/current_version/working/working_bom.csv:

"Id";"Designator";"Footprint";"Quantity";"Designation";"Supplier and ref";
1;"C5";"0805-NO";1;"10uF";;;
2;"CHG0";"CHIPLED_0805_NOOUTLINE";1;"ORANGE";;;
3;"C6,C8,C3";"0805-NO";3;"10µF";;;
4;"X4";"MICROSD";1;"microsd";;;
5;"SW1";"KMR2";1;"SPST_TACT-KMR2";;;
6;"R6";"0603-NO";1;"100K";;;
7;"C7,C1,C14";"0603-NO";3;"1uF";;;
8;"C4,C2";"0603-NO";2;"22pF";;;
9;"R3,R1";"0603-NO";2;"100k";;;
10;"X2";"XTAL3215";1;"32.768";;;
11;"@HOLE1,@HOLE0";"";2;"";;;
12;"U$34,U$35";"FIDUCIAL_1MM";2;"FIDUCIAL""";;;
13;"U$7";"ADAFRUIT_3.5MM";1;"";;;
14;"U2";"SOT23-5";1;"SPX3819-3.3";;;
15;"U$31,U$32";"MOUNTINGHOLE_2.5_PLATED";2;"MOUNTINGHOLE2.5";;;
16;"JP1";"1X16_ROUND";1;"";;;
17;"L0";"CHIPLED_0805_NOOUTLINE";1;"RED";;;
18;"L1";"CHIPLED_0805_NOOUTLINE";1;"GREEN";;;
19;"X3";"4UCONN_20329_V2";1;"microUSB";;;
20;"R4,R2";"0603-NO";2;"1K";;;
21;"JP3";"1X12_ROUND";1;"";;;
22;"U$9";"PCBFEAT-REV-040";1;"";;;
23;"D1";"SOD-123";1;"MBR120";;;
24;"R7";"0603-NO";1;"2.2K";;;
25;"U3";"SOT23-5";1;"MCP73831T-2ACI/OT";;;
26;"X1";"JSTPH2";1;"JSTPH";;;
27;"R8";"0603-NO";1;"10K\";;;
28;"U$4";"TQFN48_7MM";1;"ATSAMD21G18_QFN";;;
29;"U$14";"ADALOGGER_LOGO";1;"";;;
30;"TP1,TP2";"TESTPOINT_ROUND_1.5MM";2;"";;;
31;"U$13";"FEATHERLOGO";1;"";;;
